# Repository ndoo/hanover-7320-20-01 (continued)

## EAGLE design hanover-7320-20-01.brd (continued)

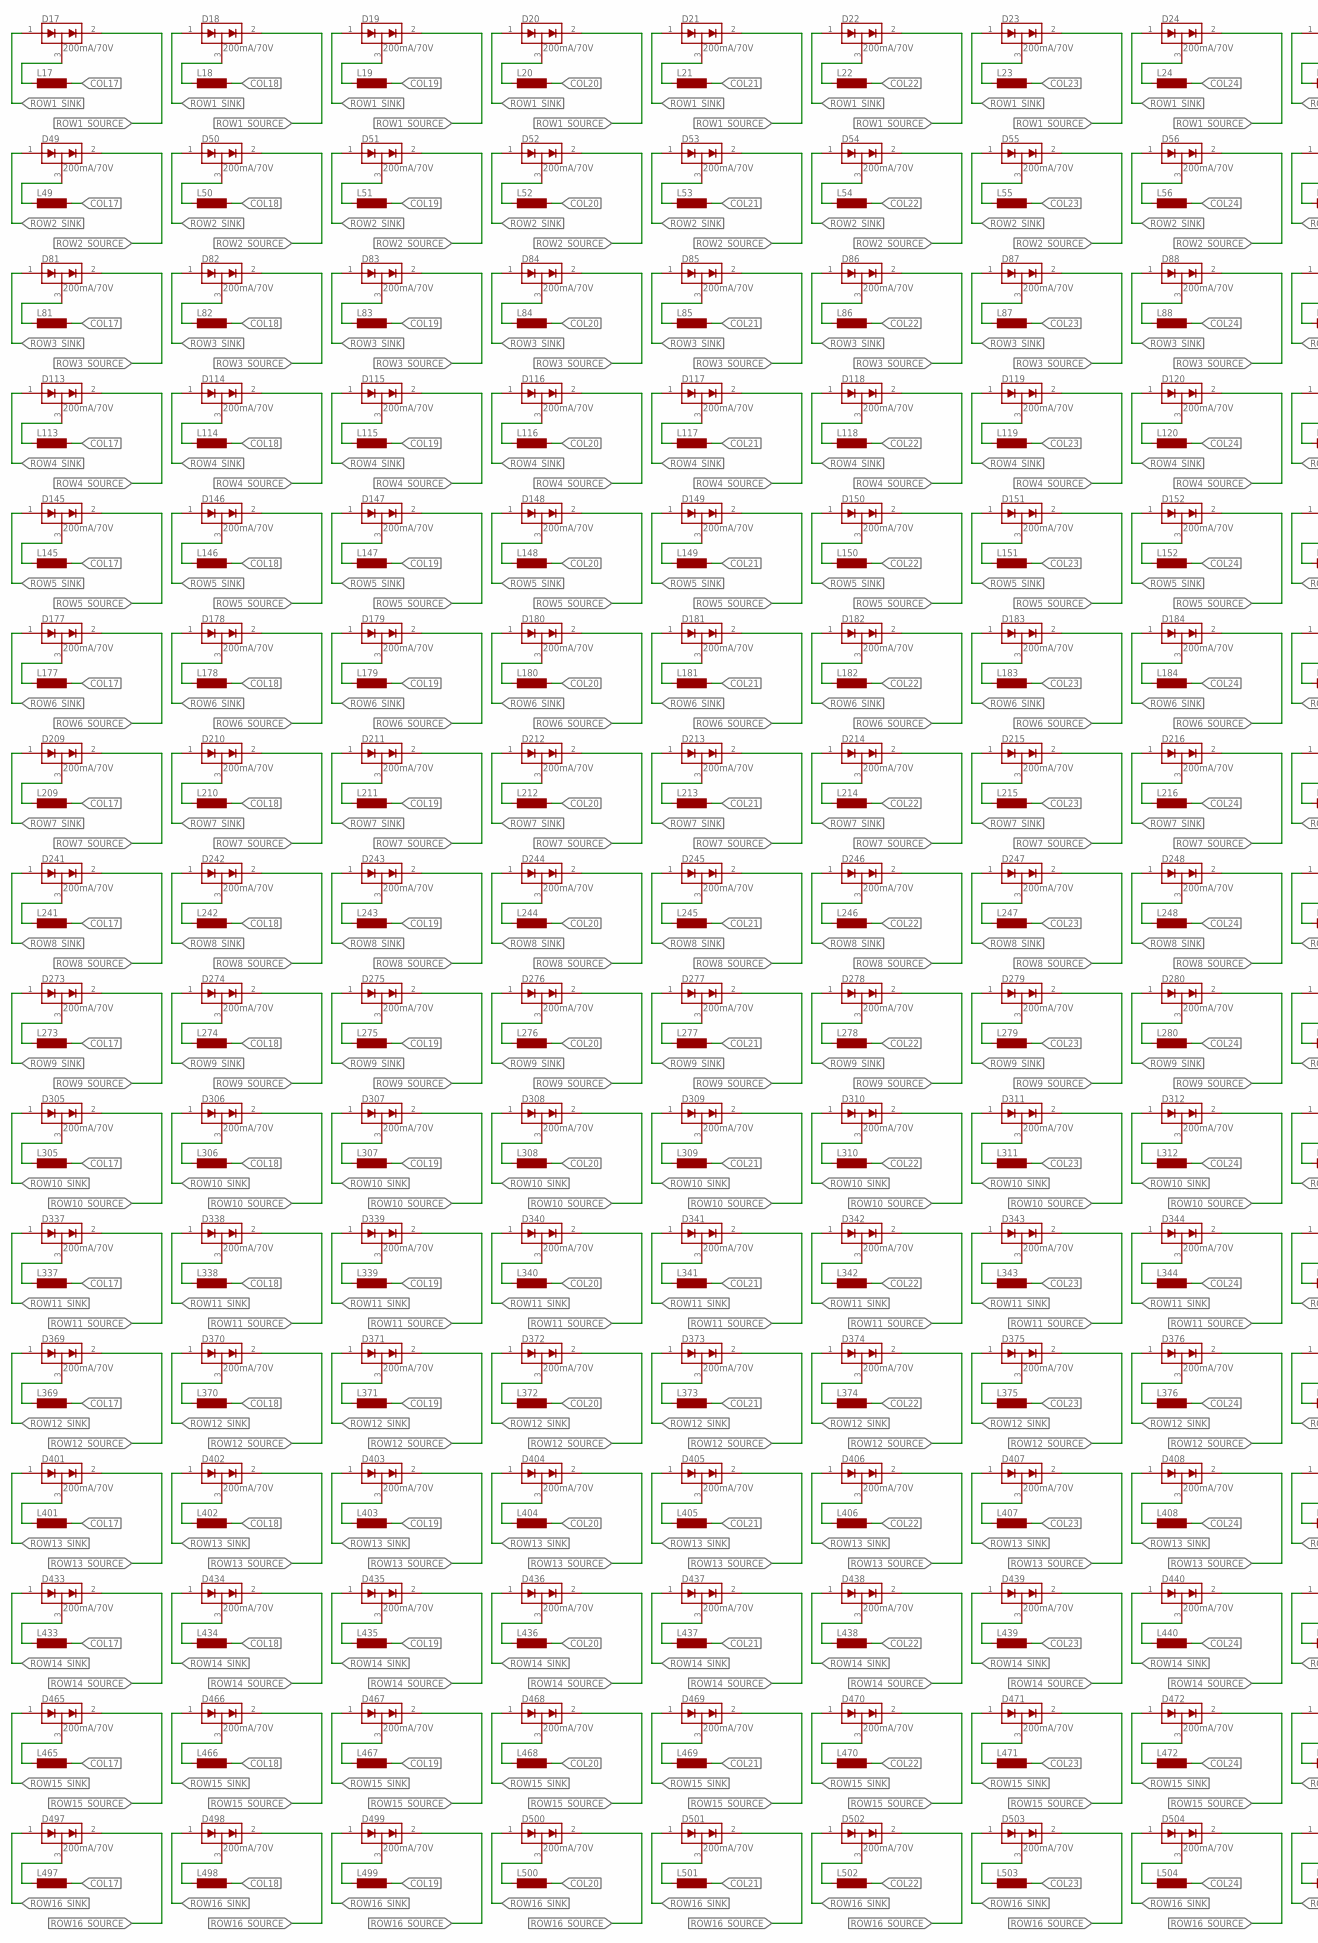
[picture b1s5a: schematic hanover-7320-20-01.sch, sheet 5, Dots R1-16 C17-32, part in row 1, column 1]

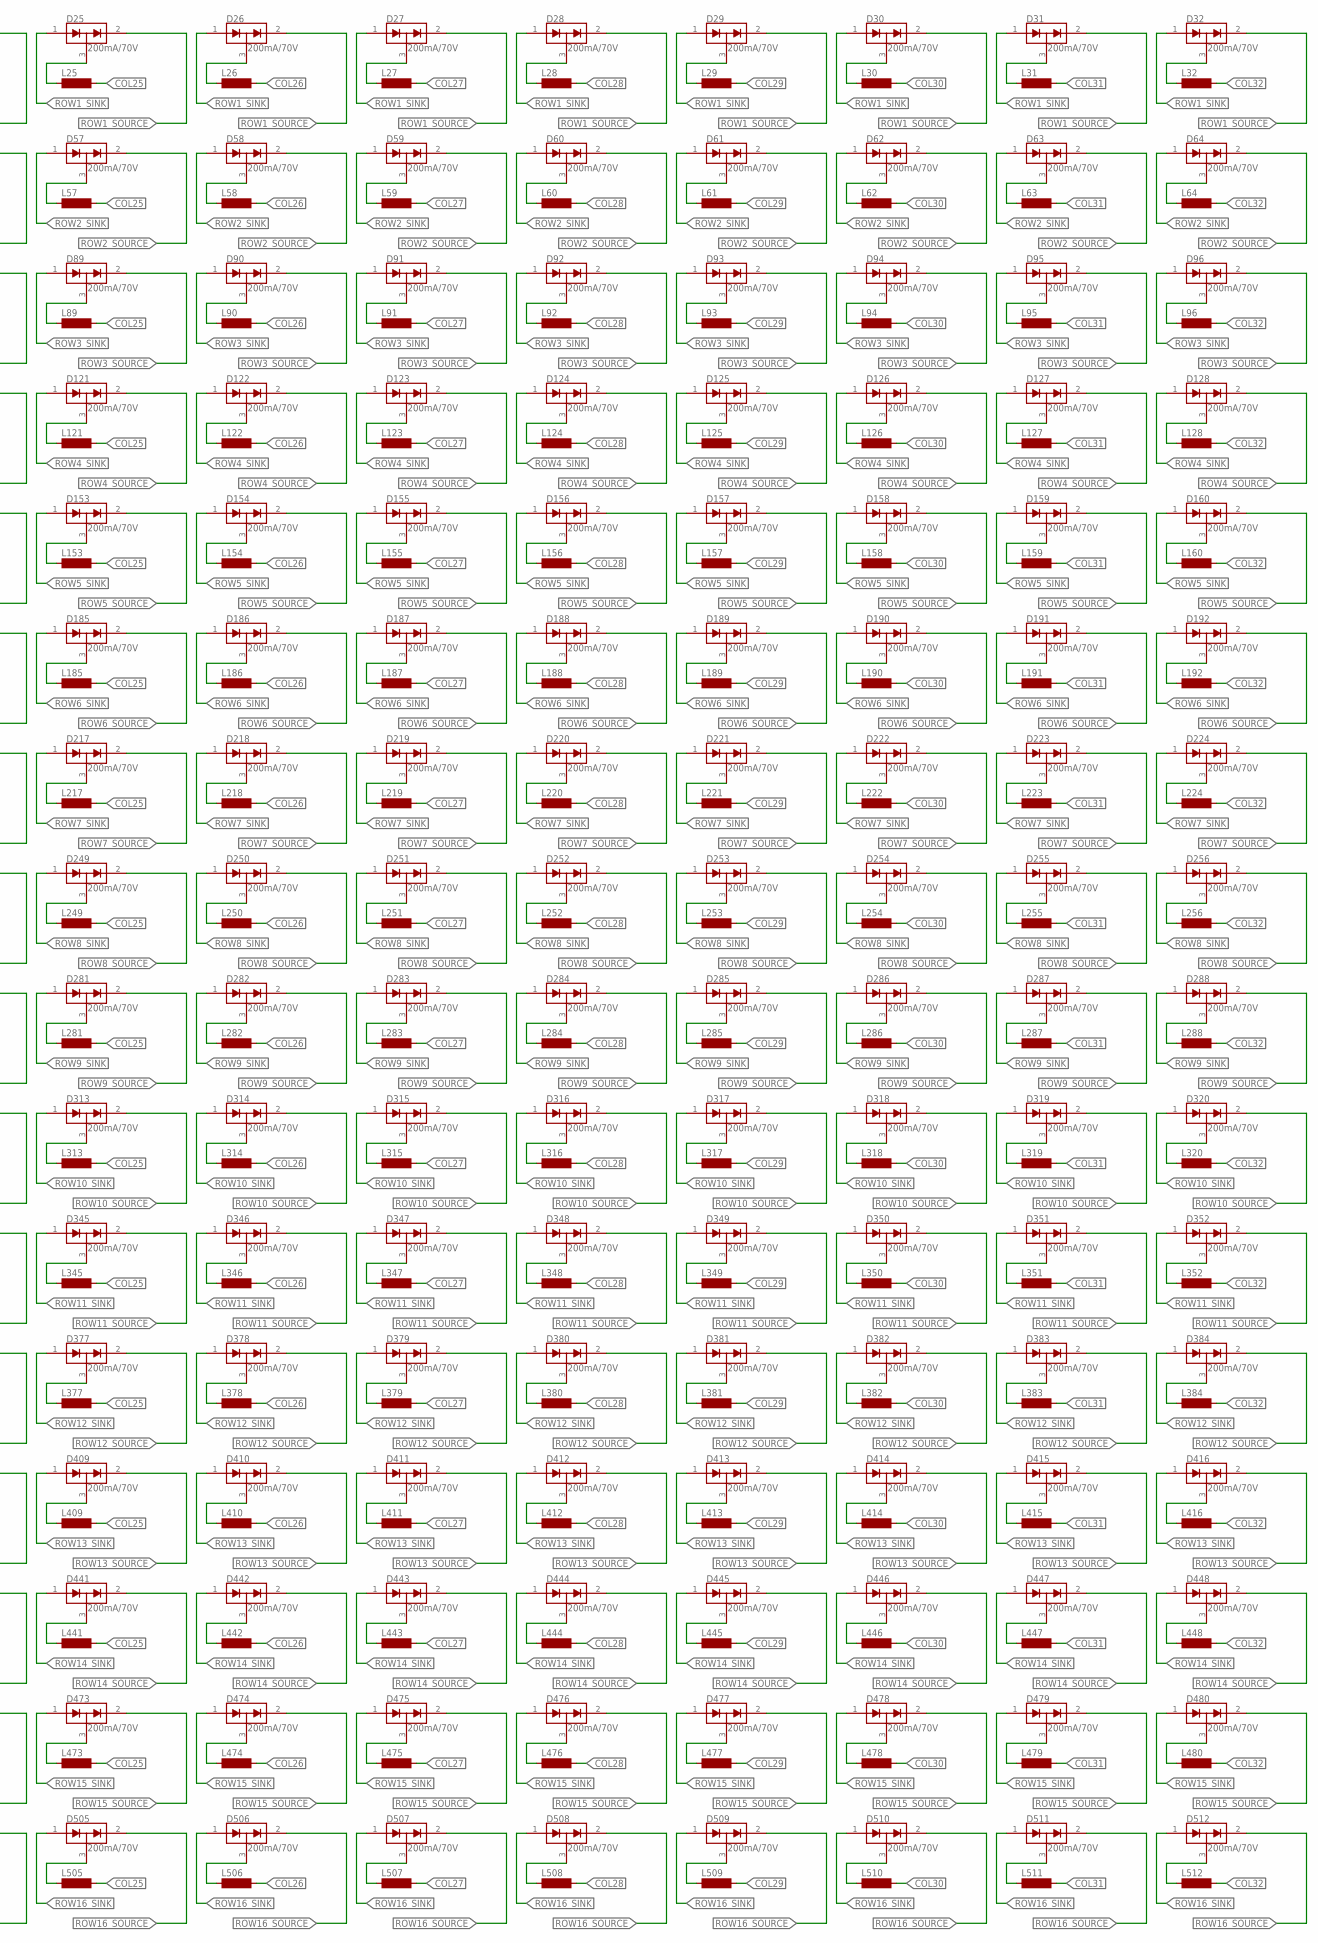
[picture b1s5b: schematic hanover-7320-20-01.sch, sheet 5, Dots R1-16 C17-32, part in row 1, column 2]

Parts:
D17, D18, D19, D20, D21, D22, D23, D24, D25, D26, D27, D28, D29, D30, D31, D32, D49, D50, D51, D52, D53, D54, D55, D56, D57, D58, D59, D60, D61, D62, D63, D64, D81, D82, D83, D84, D85, D86, D87, D88, D89, D90, D91, D92, D93, D94, D95, D96, D113, D114, D115, D116, D117, D118, D119, D120, D121, D122, D123, D124, D125, D126, D127, D128, D145, D146, D147, D148, D149, D150, D151, D152, D153, D154, D155, D156, D157, D158, D159, D160, D177, D178, D179, D180, D181, D182, D183, D184, D185, D186, D187, D188, D189, D190, D191, D192, D209, D210, D211, D212, D213, D214, D215, D216, D217, D218, D219, D220, D221, D222, D223, D224, D241, D242, D243, D244, D245, D246, D247, D248, D249, D250, D251, D252, D253, D254, D255, D256, D273, D274, D275, D276, D277, D278, D279, D280, D281, D282, D283, D284, D285, D286, D287, D288, D305, D306, D307, D308, D309, D310, D311, D312, D313, D314, D315, D316, D317, D318, D319, D320, D337, D338, D339, D340, D341, D342, D343, D344, D345, D346, D347, D348, D349, D350, D351, D352, D369, D370, D371, D372, D373, D374, D375, D376, D377, D378, D379, D380, D381, D382, D383, D384, D401, D402, D403, D404, D405, D406, D407, D408, D409, D410, D411, D412, D413, D414, D415, D416, D433, D434, D435, D436, D437, D438, D439, D440, D441, D442, D443, D444, D445, D446, D447, D448, D465, D466, D467, D468, D469, D470, D471, D472, D473, D474, D475, D476, D477, D478, D479, D480, D497, D498, D499, D500, D501, D502, D503, D504, D505, D506, D507, D508, D509, D510, D511, D512: 200mA/70V; SOT23-3
L17, L18, L19, L20, L21, L22, L23, L24, L25, L26, L27, L28, L29, L30, L31, L32, L49, L50, L51, L52, L53, L54, L55, L56, L57, L58, L59, L60, L61, L62, L63, L64, L81, L82, L83, L84, L85, L86, L87, L88, L89, L90, L91, L92, L93, L94, L95, L96, L113, L114, L115, L116, L117, L118, L119, L120, L121, L122, L123, L124, L125, L126, L127, L128, L145, L146, L147, L148, L149, L150, L151, L152, L153, L154, L155, L156, L157, L158, L159, L160, L177, L178, L179, L180, L181, L182, L183, L184, L185, L186, L187, L188, L189, L190, L191, L192, L209, L210, L211, L212, L213, L214, L215, L216, L217, L218, L219, L220, L221, L222, L223, L224, L241, L242, L243, L244, L245, L246, L247, L248, L249, L250, L251, L252, L253, L254, L255, L256, L273, L274, L275, L276, L277, L278, L279, L280, L281, L282, L283, L284, L285, L286, L287, L288, L305, L306, L307, L308, L309, L310, L311, L312, L313, L314, L315, L316, L317, L318, L319, L320, L337, L338, L339, L340, L341, L342, L343, L344, L345, L346, L347, L348, L349, L350, L351, L352, L369, L370, L371, L372, L373, L374, L375, L376, L377, L378, L379, L380, L381, L382, L383, L384, L401, L402, L403, L404, L405, L406, L407, L408, L409, L410, L411, L412, L413, L414, L415, L416, L433, L434, L435, L436, L437, L438, L439, L440, L441, L442, L443, L444, L445, L446, L447, L448, L465, L466, L467, L468, L469, L470, L471, L472, L473, L474, L475, L476, L477, L478, L479, L480, L497, L498, L499, L500, L501, L502, L503, L504, L505, L506, L507, L508, L509, L510, L511, L512: SD8

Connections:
COL17: L17.2, L49.2, L81.2, L113.2, L145.2, L177.2, L209.2, L241.2, L273.2, L305.2, L337.2, L369.2, L401.2, L433.2, L465.2, L497.2; also elsewhere on the board
COL18: L18.2, L50.2, L82.2, L114.2, L146.2, L178.2, L210.2, L242.2, L274.2, L306.2, L338.2, L370.2, L402.2, L434.2, L466.2, L498.2; also elsewhere on the board
COL19: L19.2, L51.2, L83.2, L115.2, L147.2, L179.2, L211.2, L243.2, L275.2, L307.2, L339.2, L371.2, L403.2, L435.2, L467.2, L499.2; also elsewhere on the board
COL20: L20.2, L52.2, L84.2, L116.2, L148.2, L180.2, L212.2, L244.2, L276.2, L308.2, L340.2, L372.2, L404.2, L436.2, L468.2, L500.2; also elsewhere on the board
COL21: L21.2, L53.2, L85.2, L117.2, L149.2, L181.2, L213.2, L245.2, L277.2, L309.2, L341.2, L373.2, L405.2, L437.2, L469.2, L501.2; also elsewhere on the board
COL22: L22.2, L54.2, L86.2, L118.2, L150.2, L182.2, L214.2, L246.2, L278.2, L310.2, L342.2, L374.2, L406.2, L438.2, L470.2, L502.2; also elsewhere on the board
COL23: L23.2, L55.2, L87.2, L119.2, L151.2, L183.2, L215.2, L247.2, L279.2, L311.2, L343.2, L375.2, L407.2, L439.2, L471.2, L503.2; also elsewhere on the board
COL24: L24.2, L56.2, L88.2, L120.2, L152.2, L184.2, L216.2, L248.2, L280.2, L312.2, L344.2, L376.2, L408.2, L440.2, L472.2, L504.2; also elsewhere on the board
COL25: L25.2, L57.2, L89.2, L121.2, L153.2, L185.2, L217.2, L249.2, L281.2, L313.2, L345.2, L377.2, L409.2, L441.2, L473.2, L505.2; also elsewhere on the board
COL26: L26.2, L58.2, L90.2, L122.2, L154.2, L186.2, L218.2, L250.2, L282.2, L314.2, L346.2, L378.2, L410.2, L442.2, L474.2, L506.2; also elsewhere on the board
COL27: L27.2, L59.2, L91.2, L123.2, L155.2, L187.2, L219.2, L251.2, L283.2, L315.2, L347.2, L379.2, L411.2, L443.2, L475.2, L507.2; also elsewhere on the board
COL28: L28.2, L60.2, L92.2, L124.2, L156.2, L188.2, L220.2, L252.2, L284.2, L316.2, L348.2, L380.2, L412.2, L444.2, L476.2, L508.2; also elsewhere on the board
COL29: L29.2, L61.2, L93.2, L125.2, L157.2, L189.2, L221.2, L253.2, L285.2, L317.2, L349.2, L381.2, L413.2, L445.2, L477.2, L509.2; also elsewhere on the board
COL30: L30.2, L62.2, L94.2, L126.2, L158.2, L190.2, L222.2, L254.2, L286.2, L318.2, L350.2, L382.2, L414.2, L446.2, L478.2, L510.2; also elsewhere on the board
COL31: L31.2, L63.2, L95.2, L127.2, L159.2, L191.2, L223.2, L255.2, L287.2, L319.2, L351.2, L383.2, L415.2, L447.2, L479.2, L511.2; also elsewhere on the board
COL32: L32.2, L64.2, L96.2, L128.2, L160.2, L192.2, L224.2, L256.2, L288.2, L320.2, L352.2, L384.2, L416.2, L448.2, L480.2, L512.2; also elsewhere on the board
unnamed: D17.3 (COM), L17.1
unnamed: D18.3 (COM), L18.1
unnamed: D19.3 (COM), L19.1
unnamed: D20.3 (COM), L20.1
unnamed: D21.3 (COM), L21.1
unnamed: D22.3 (COM), L22.1
unnamed: D23.3 (COM), L23.1
unnamed: D24.3 (COM), L24.1
unnamed: D25.3 (COM), L25.1
unnamed: D26.3 (COM), L26.1
unnamed: D27.3 (COM), L27.1
unnamed: D28.3 (COM), L28.1
unnamed: D29.3 (COM), L29.1
unnamed: D30.3 (COM), L30.1
unnamed: D31.3 (COM), L31.1
unnamed: D32.3 (COM), L32.1
unnamed: D49.3 (COM), L49.1
unnamed: D50.3 (COM), L50.1
unnamed: D51.3 (COM), L51.1
unnamed: D52.3 (COM), L52.1
unnamed: D53.3 (COM), L53.1
unnamed: D54.3 (COM), L54.1
unnamed: D55.3 (COM), L55.1
unnamed: D56.3 (COM), L56.1
unnamed: D57.3 (COM), L57.1
unnamed: D58.3 (COM), L58.1
unnamed: D59.3 (COM), L59.1
unnamed: D60.3 (COM), L60.1
unnamed: D61.3 (COM), L61.1
unnamed: D62.3 (COM), L62.1
unnamed: D63.3 (COM), L63.1
unnamed: D64.3 (COM), L64.1
unnamed: D81.3 (COM), L81.1
unnamed: D82.3 (COM), L82.1
unnamed: D83.3 (COM), L83.1
unnamed: D84.3 (COM), L84.1
unnamed: D85.3 (COM), L85.1
unnamed: D86.3 (COM), L86.1
unnamed: D87.3 (COM), L87.1
unnamed: D88.3 (COM), L88.1
unnamed: D89.3 (COM), L89.1
unnamed: D90.3 (COM), L90.1
unnamed: D91.3 (COM), L91.1
unnamed: D92.3 (COM), L92.1
unnamed: D93.3 (COM), L93.1
unnamed: D94.3 (COM), L94.1
unnamed: D95.3 (COM), L95.1
unnamed: D96.3 (COM), L96.1
unnamed: D113.3 (COM), L113.1
unnamed: D114.3 (COM), L114.1
unnamed: D115.3 (COM), L115.1
unnamed: D116.3 (COM), L116.1
unnamed: D117.3 (COM), L117.1
unnamed: D118.3 (COM), L118.1
unnamed: D119.3 (COM), L119.1
unnamed: D120.3 (COM), L120.1
unnamed: D121.3 (COM), L121.1
unnamed: D122.3 (COM), L122.1
unnamed: D123.3 (COM), L123.1
unnamed: D124.3 (COM), L124.1
unnamed: D125.3 (COM), L125.1
unnamed: D126.3 (COM), L126.1
unnamed: D127.3 (COM), L127.1
unnamed: D128.3 (COM), L128.1
unnamed: D145.3 (COM), L145.1
unnamed: D146.3 (COM), L146.1
unnamed: D147.3 (COM), L147.1
unnamed: D148.3 (COM), L148.1
unnamed: D149.3 (COM), L149.1
unnamed: D150.3 (COM), L150.1
unnamed: D151.3 (COM), L151.1
unnamed: D152.3 (COM), L152.1
unnamed: D153.3 (COM), L153.1
unnamed: D154.3 (COM), L154.1
unnamed: D155.3 (COM), L155.1
unnamed: D156.3 (COM), L156.1
unnamed: D157.3 (COM), L157.1
unnamed: D158.3 (COM), L158.1
unnamed: D159.3 (COM), L159.1
unnamed: D160.3 (COM), L160.1
unnamed: D177.3 (COM), L177.1
unnamed: D178.3 (COM), L178.1
unnamed: D179.3 (COM), L179.1
unnamed: D180.3 (COM), L180.1
unnamed: D181.3 (COM), L181.1
unnamed: D182.3 (COM), L182.1
unnamed: D183.3 (COM), L183.1
unnamed: D184.3 (COM), L184.1
unnamed: D185.3 (COM), L185.1
unnamed: D186.3 (COM), L186.1
unnamed: D187.3 (COM), L187.1
unnamed: D188.3 (COM), L188.1
unnamed: D189.3 (COM), L189.1
unnamed: D190.3 (COM), L190.1
unnamed: D191.3 (COM), L191.1
unnamed: D192.3 (COM), L192.1
unnamed: D209.3 (COM), L209.1
unnamed: D210.3 (COM), L210.1
unnamed: D211.3 (COM), L211.1
unnamed: D212.3 (COM), L212.1
unnamed: D213.3 (COM), L213.1
unnamed: D214.3 (COM), L214.1
unnamed: D215.3 (COM), L215.1
unnamed: D216.3 (COM), L216.1
unnamed: D217.3 (COM), L217.1
unnamed: D218.3 (COM), L218.1
unnamed: D219.3 (COM), L219.1
unnamed: D220.3 (COM), L220.1
unnamed: D221.3 (COM), L221.1
unnamed: D222.3 (COM), L222.1
unnamed: D223.3 (COM), L223.1
unnamed: D224.3 (COM), L224.1
unnamed: D241.3 (COM), L241.1
unnamed: D242.3 (COM), L242.1
unnamed: D243.3 (COM), L243.1
unnamed: D244.3 (COM), L244.1
unnamed: D245.3 (COM), L245.1
unnamed: D246.3 (COM), L246.1
unnamed: D247.3 (COM), L247.1
unnamed: D248.3 (COM), L248.1
unnamed: D249.3 (COM), L249.1
unnamed: D250.3 (COM), L250.1
unnamed: D251.3 (COM), L251.1
unnamed: D252.3 (COM), L252.1
unnamed: D253.3 (COM), L253.1
unnamed: D254.3 (COM), L254.1
unnamed: D255.3 (COM), L255.1
unnamed: D256.3 (COM), L256.1
unnamed: D273.3 (COM), L273.1
unnamed: D274.3 (COM), L274.1
unnamed: D275.3 (COM), L275.1
unnamed: D276.3 (COM), L276.1
unnamed: D277.3 (COM), L277.1
unnamed: D278.3 (COM), L278.1
unnamed: D279.3 (COM), L279.1
unnamed: D280.3 (COM), L280.1
unnamed: D281.3 (COM), L281.1
unnamed: D282.3 (COM), L282.1
unnamed: D283.3 (COM), L283.1
unnamed: D284.3 (COM), L284.1
unnamed: D285.3 (COM), L285.1
unnamed: D286.3 (COM), L286.1
unnamed: D287.3 (COM), L287.1
unnamed: D288.3 (COM), L288.1
unnamed: D305.3 (COM), L305.1
unnamed: D306.3 (COM), L306.1
unnamed: D307.3 (COM), L307.1
unnamed: D308.3 (COM), L308.1
unnamed: D309.3 (COM), L309.1
unnamed: D310.3 (COM), L310.1
unnamed: D311.3 (COM), L311.1
unnamed: D312.3 (COM), L312.1
unnamed: D313.3 (COM), L313.1
unnamed: D314.3 (COM), L314.1
unnamed: D315.3 (COM), L315.1
unnamed: D316.3 (COM), L316.1
unnamed: D317.3 (COM), L317.1
unnamed: D318.3 (COM), L318.1
unnamed: D319.3 (COM), L319.1
unnamed: D320.3 (COM), L320.1
unnamed: D337.3 (COM), L337.1
unnamed: D338.3 (COM), L338.1
unnamed: D339.3 (COM), L339.1
unnamed: D340.3 (COM), L340.1
unnamed: D341.3 (COM), L341.1
unnamed: D342.3 (COM), L342.1
unnamed: D343.3 (COM), L343.1
unnamed: D344.3 (COM), L344.1
unnamed: D345.3 (COM), L345.1
unnamed: D346.3 (COM), L346.1
unnamed: D347.3 (COM), L347.1
unnamed: D348.3 (COM), L348.1
unnamed: D349.3 (COM), L349.1
unnamed: D350.3 (COM), L350.1
unnamed: D351.3 (COM), L351.1
unnamed: D352.3 (COM), L352.1
unnamed: D369.3 (COM), L369.1
unnamed: D370.3 (COM), L370.1
unnamed: D371.3 (COM), L371.1
unnamed: D372.3 (COM), L372.1
unnamed: D373.3 (COM), L373.1
unnamed: D374.3 (COM), L374.1
unnamed: D375.3 (COM), L375.1
unnamed: D376.3 (COM), L376.1
unnamed: D377.3 (COM), L377.1
unnamed: D378.3 (COM), L378.1
unnamed: D379.3 (COM), L379.1
unnamed: D380.3 (COM), L380.1
unnamed: D381.3 (COM), L381.1
unnamed: D382.3 (COM), L382.1
unnamed: D383.3 (COM), L383.1
unnamed: D384.3 (COM), L384.1
unnamed: D401.3 (COM), L401.1
unnamed: D402.3 (COM), L402.1
unnamed: D403.3 (COM), L403.1
unnamed: D404.3 (COM), L404.1
unnamed: D405.3 (COM), L405.1
unnamed: D406.3 (COM), L406.1
unnamed: D407.3 (COM), L407.1
unnamed: D408.3 (COM), L408.1
unnamed: D409.3 (COM), L409.1
unnamed: D410.3 (COM), L410.1
unnamed: D411.3 (COM), L411.1
unnamed: D412.3 (COM), L412.1
unnamed: D413.3 (COM), L413.1
unnamed: D414.3 (COM), L414.1
unnamed: D415.3 (COM), L415.1
unnamed: D416.3 (COM), L416.1
unnamed: D433.3 (COM), L433.1
unnamed: D434.3 (COM), L434.1
unnamed: D435.3 (COM), L435.1
unnamed: D436.3 (COM), L436.1
unnamed: D437.3 (COM), L437.1
unnamed: D438.3 (COM), L438.1
unnamed: D439.3 (COM), L439.1
unnamed: D440.3 (COM), L440.1
unnamed: D441.3 (COM), L441.1
unnamed: D442.3 (COM), L442.1
unnamed: D443.3 (COM), L443.1
unnamed: D444.3 (COM), L444.1
unnamed: D445.3 (COM), L445.1
unnamed: D446.3 (COM), L446.1
unnamed: D447.3 (COM), L447.1
unnamed: D448.3 (COM), L448.1
unnamed: D465.3 (COM), L465.1
unnamed: D466.3 (COM), L466.1
unnamed: D467.3 (COM), L467.1
unnamed: D468.3 (COM), L468.1
unnamed: D469.3 (COM), L469.1
unnamed: D470.3 (COM), L470.1
unnamed: D471.3 (COM), L471.1
unnamed: D472.3 (COM), L472.1
unnamed: D473.3 (COM), L473.1
unnamed: D474.3 (COM), L474.1
unnamed: D475.3 (COM), L475.1
unnamed: D476.3 (COM), L476.1
unnamed: D477.3 (COM), L477.1
unnamed: D478.3 (COM), L478.1
unnamed: D479.3 (COM), L479.1
unnamed: D480.3 (COM), L480.1
unnamed: D497.3 (COM), L497.1
unnamed: D498.3 (COM), L498.1
unnamed: D499.3 (COM), L499.1
unnamed: D500.3 (COM), L500.1
unnamed: D501.3 (COM), L501.1
unnamed: D502.3 (COM), L502.1
unnamed: D503.3 (COM), L503.1
unnamed: D504.3 (COM), L504.1
unnamed: D505.3 (COM), L505.1
unnamed: D506.3 (COM), L506.1
unnamed: D507.3 (COM), L507.1
unnamed: D508.3 (COM), L508.1
unnamed: D509.3 (COM), L509.1
unnamed: D510.3 (COM), L510.1
unnamed: D511.3 (COM), L511.1
unnamed: D512.3 (COM), L512.1
ROW1_SINK: D17.1 (A1), D18.1 (A1), D19.1 (A1), D20.1 (A1), D21.1 (A1), D22.1 (A1), D23.1 (A1), D24.1 (A1), D25.1 (A1), D26.1 (A1), D27.1 (A1), D28.1 (A1), D29.1 (A1), D30.1 (A1), D31.1 (A1), D32.1 (A1); also elsewhere on the board
ROW1_SOURCE: D17.2 (C2), D18.2 (C2), D19.2 (C2), D20.2 (C2), D21.2 (C2), D22.2 (C2), D23.2 (C2), D24.2 (C2), D25.2 (C2), D26.2 (C2), D27.2 (C2), D28.2 (C2), D29.2 (C2), D30.2 (C2), D31.2 (C2), D32.2 (C2); also elsewhere on the board
ROW2_SINK: D49.1 (A1), D50.1 (A1), D51.1 (A1), D52.1 (A1), D53.1 (A1), D54.1 (A1), D55.1 (A1), D56.1 (A1), D57.1 (A1), D58.1 (A1), D59.1 (A1), D60.1 (A1), D61.1 (A1), D62.1 (A1), D63.1 (A1), D64.1 (A1); also elsewhere on the board
ROW2_SOURCE: D49.2 (C2), D50.2 (C2), D51.2 (C2), D52.2 (C2), D53.2 (C2), D54.2 (C2), D55.2 (C2), D56.2 (C2), D57.2 (C2), D58.2 (C2), D59.2 (C2), D60.2 (C2), D61.2 (C2), D62.2 (C2), D63.2 (C2), D64.2 (C2); also elsewhere on the board
ROW3_SINK: D81.1 (A1), D82.1 (A1), D83.1 (A1), D84.1 (A1), D85.1 (A1), D86.1 (A1), D87.1 (A1), D88.1 (A1), D89.1 (A1), D90.1 (A1), D91.1 (A1), D92.1 (A1), D93.1 (A1), D94.1 (A1), D95.1 (A1), D96.1 (A1); also elsewhere on the board
ROW3_SOURCE: D81.2 (C2), D82.2 (C2), D83.2 (C2), D84.2 (C2), D85.2 (C2), D86.2 (C2), D87.2 (C2), D88.2 (C2), D89.2 (C2), D90.2 (C2), D91.2 (C2), D92.2 (C2), D93.2 (C2), D94.2 (C2), D95.2 (C2), D96.2 (C2); also elsewhere on the board
ROW4_SINK: D113.1 (A1), D114.1 (A1), D115.1 (A1), D116.1 (A1), D117.1 (A1), D118.1 (A1), D119.1 (A1), D120.1 (A1), D121.1 (A1), D122.1 (A1), D123.1 (A1), D124.1 (A1), D125.1 (A1), D126.1 (A1), D127.1 (A1), D128.1 (A1); also elsewhere on the board
ROW4_SOURCE: D113.2 (C2), D114.2 (C2), D115.2 (C2), D116.2 (C2), D117.2 (C2), D118.2 (C2), D119.2 (C2), D120.2 (C2), D121.2 (C2), D122.2 (C2), D123.2 (C2), D124.2 (C2), D125.2 (C2), D126.2 (C2), D127.2 (C2), D128.2 (C2); also elsewhere on the board
ROW5_SINK: D145.1 (A1), D146.1 (A1), D147.1 (A1), D148.1 (A1), D149.1 (A1), D150.1 (A1), D151.1 (A1), D152.1 (A1), D153.1 (A1), D154.1 (A1), D155.1 (A1), D156.1 (A1), D157.1 (A1), D158.1 (A1), D159.1 (A1), D160.1 (A1); also elsewhere on the board
ROW5_SOURCE: D145.2 (C2), D146.2 (C2), D147.2 (C2), D148.2 (C2), D149.2 (C2), D150.2 (C2), D151.2 (C2), D152.2 (C2), D153.2 (C2), D154.2 (C2), D155.2 (C2), D156.2 (C2), D157.2 (C2), D158.2 (C2), D159.2 (C2), D160.2 (C2); also elsewhere on the board
ROW6_SINK: D177.1 (A1), D178.1 (A1), D179.1 (A1), D180.1 (A1), D181.1 (A1), D182.1 (A1), D183.1 (A1), D184.1 (A1), D185.1 (A1), D186.1 (A1), D187.1 (A1), D188.1 (A1), D189.1 (A1), D190.1 (A1), D191.1 (A1), D192.1 (A1); also elsewhere on the board
ROW6_SOURCE: D177.2 (C2), D178.2 (C2), D179.2 (C2), D180.2 (C2), D181.2 (C2), D182.2 (C2), D183.2 (C2), D184.2 (C2), D185.2 (C2), D186.2 (C2), D187.2 (C2), D188.2 (C2), D189.2 (C2), D190.2 (C2), D191.2 (C2), D192.2 (C2); also elsewhere on the board
ROW7_SINK: D209.1 (A1), D210.1 (A1), D211.1 (A1), D212.1 (A1), D213.1 (A1), D214.1 (A1), D215.1 (A1), D216.1 (A1), D217.1 (A1), D218.1 (A1), D219.1 (A1), D220.1 (A1), D221.1 (A1), D222.1 (A1), D223.1 (A1), D224.1 (A1); also elsewhere on the board
ROW7_SOURCE: D209.2 (C2), D210.2 (C2), D211.2 (C2), D212.2 (C2), D213.2 (C2), D214.2 (C2), D215.2 (C2), D216.2 (C2), D217.2 (C2), D218.2 (C2), D219.2 (C2), D220.2 (C2), D221.2 (C2), D222.2 (C2), D223.2 (C2), D224.2 (C2); also elsewhere on the board
ROW8_SINK: D241.1 (A1), D242.1 (A1), D243.1 (A1), D244.1 (A1), D245.1 (A1), D246.1 (A1), D247.1 (A1), D248.1 (A1), D249.1 (A1), D250.1 (A1), D251.1 (A1), D252.1 (A1), D253.1 (A1), D254.1 (A1), D255.1 (A1), D256.1 (A1); also elsewhere on the board
ROW8_SOURCE: D241.2 (C2), D242.2 (C2), D243.2 (C2), D244.2 (C2), D245.2 (C2), D246.2 (C2), D247.2 (C2), D248.2 (C2), D249.2 (C2), D250.2 (C2), D251.2 (C2), D252.2 (C2), D253.2 (C2), D254.2 (C2), D255.2 (C2), D256.2 (C2); also elsewhere on the board
ROW9_SINK: D273.1 (A1), D274.1 (A1), D275.1 (A1), D276.1 (A1), D277.1 (A1), D278.1 (A1), D279.1 (A1), D280.1 (A1), D281.1 (A1), D282.1 (A1), D283.1 (A1), D284.1 (A1), D285.1 (A1), D286.1 (A1), D287.1 (A1), D288.1 (A1); also elsewhere on the board
ROW9_SOURCE: D273.2 (C2), D274.2 (C2), D275.2 (C2), D276.2 (C2), D277.2 (C2), D278.2 (C2), D279.2 (C2), D280.2 (C2), D281.2 (C2), D282.2 (C2), D283.2 (C2), D284.2 (C2), D285.2 (C2), D286.2 (C2), D287.2 (C2), D288.2 (C2); also elsewhere on the board
ROW10_SINK: D305.1 (A1), D306.1 (A1), D307.1 (A1), D308.1 (A1), D309.1 (A1), D310.1 (A1), D311.1 (A1), D312.1 (A1), D313.1 (A1), D314.1 (A1), D315.1 (A1), D316.1 (A1), D317.1 (A1), D318.1 (A1), D319.1 (A1), D320.1 (A1); also elsewhere on the board
ROW10_SOURCE: D305.2 (C2), D306.2 (C2), D307.2 (C2), D308.2 (C2), D309.2 (C2), D310.2 (C2), D311.2 (C2), D312.2 (C2), D313.2 (C2), D314.2 (C2), D315.2 (C2), D316.2 (C2), D317.2 (C2), D318.2 (C2), D319.2 (C2), D320.2 (C2); also elsewhere on the board
ROW11_SINK: D337.1 (A1), D338.1 (A1), D339.1 (A1), D340.1 (A1), D341.1 (A1), D342.1 (A1), D343.1 (A1), D344.1 (A1), D345.1 (A1), D346.1 (A1), D347.1 (A1), D348.1 (A1), D349.1 (A1), D350.1 (A1), D351.1 (A1), D352.1 (A1); also elsewhere on the board
ROW11_SOURCE: D337.2 (C2), D338.2 (C2), D339.2 (C2), D340.2 (C2), D341.2 (C2), D342.2 (C2), D343.2 (C2), D344.2 (C2), D345.2 (C2), D346.2 (C2), D347.2 (C2), D348.2 (C2), D349.2 (C2), D350.2 (C2), D351.2 (C2), D352.2 (C2); also elsewhere on the board
ROW12_SINK: D369.1 (A1), D370.1 (A1), D371.1 (A1), D372.1 (A1), D373.1 (A1), D374.1 (A1), D375.1 (A1), D376.1 (A1), D377.1 (A1), D378.1 (A1), D379.1 (A1), D380.1 (A1), D381.1 (A1), D382.1 (A1), D383.1 (A1), D384.1 (A1); also elsewhere on the board
ROW12_SOURCE: D369.2 (C2), D370.2 (C2), D371.2 (C2), D372.2 (C2), D373.2 (C2), D374.2 (C2), D375.2 (C2), D376.2 (C2), D377.2 (C2), D378.2 (C2), D379.2 (C2), D380.2 (C2), D381.2 (C2), D382.2 (C2), D383.2 (C2), D384.2 (C2); also elsewhere on the board
ROW13_SINK: D401.1 (A1), D402.1 (A1), D403.1 (A1), D404.1 (A1), D405.1 (A1), D406.1 (A1), D407.1 (A1), D408.1 (A1), D409.1 (A1), D410.1 (A1), D411.1 (A1), D412.1 (A1), D413.1 (A1), D414.1 (A1), D415.1 (A1), D416.1 (A1); also elsewhere on the board
ROW13_SOURCE: D401.2 (C2), D402.2 (C2), D403.2 (C2), D404.2 (C2), D405.2 (C2), D406.2 (C2), D407.2 (C2), D408.2 (C2), D409.2 (C2), D410.2 (C2), D411.2 (C2), D412.2 (C2), D413.2 (C2), D414.2 (C2), D415.2 (C2), D416.2 (C2); also elsewhere on the board
ROW14_SINK: D433.1 (A1), D434.1 (A1), D435.1 (A1), D436.1 (A1), D437.1 (A1), D438.1 (A1), D439.1 (A1), D440.1 (A1), D441.1 (A1), D442.1 (A1), D443.1 (A1), D444.1 (A1), D445.1 (A1), D446.1 (A1), D447.1 (A1), D448.1 (A1); also elsewhere on the board
ROW14_SOURCE: D433.2 (C2), D434.2 (C2), D435.2 (C2), D436.2 (C2), D437.2 (C2), D438.2 (C2), D439.2 (C2), D440.2 (C2), D441.2 (C2), D442.2 (C2), D443.2 (C2), D444.2 (C2), D445.2 (C2), D446.2 (C2), D447.2 (C2), D448.2 (C2); also elsewhere on the board
ROW15_SINK: D465.1 (A1), D466.1 (A1), D467.1 (A1), D468.1 (A1), D469.1 (A1), D470.1 (A1), D471.1 (A1), D472.1 (A1), D473.1 (A1), D474.1 (A1), D475.1 (A1), D476.1 (A1), D477.1 (A1), D478.1 (A1), D479.1 (A1), D480.1 (A1); also elsewhere on the board
ROW15_SOURCE: D465.2 (C2), D466.2 (C2), D467.2 (C2), D468.2 (C2), D469.2 (C2), D470.2 (C2), D471.2 (C2), D472.2 (C2), D473.2 (C2), D474.2 (C2), D475.2 (C2), D476.2 (C2), D477.2 (C2), D478.2 (C2), D479.2 (C2), D480.2 (C2); also elsewhere on the board
ROW16_SINK: D497.1 (A1), D498.1 (A1), D499.1 (A1), D500.1 (A1), D501.1 (A1), D502.1 (A1), D503.1 (A1), D504.1 (A1), D505.1 (A1), D506.1 (A1), D507.1 (A1), D508.1 (A1), D509.1 (A1), D510.1 (A1), D511.1 (A1), D512.1 (A1); also elsewhere on the board
ROW16_SOURCE: D497.2 (C2), D498.2 (C2), D499.2 (C2), D500.2 (C2), D501.2 (C2), D502.2 (C2), D503.2 (C2), D504.2 (C2), D505.2 (C2), D506.2 (C2), D507.2 (C2), D508.2 (C2), D509.2 (C2), D510.2 (C2), D511.2 (C2), D512.2 (C2); also elsewhere on the board
